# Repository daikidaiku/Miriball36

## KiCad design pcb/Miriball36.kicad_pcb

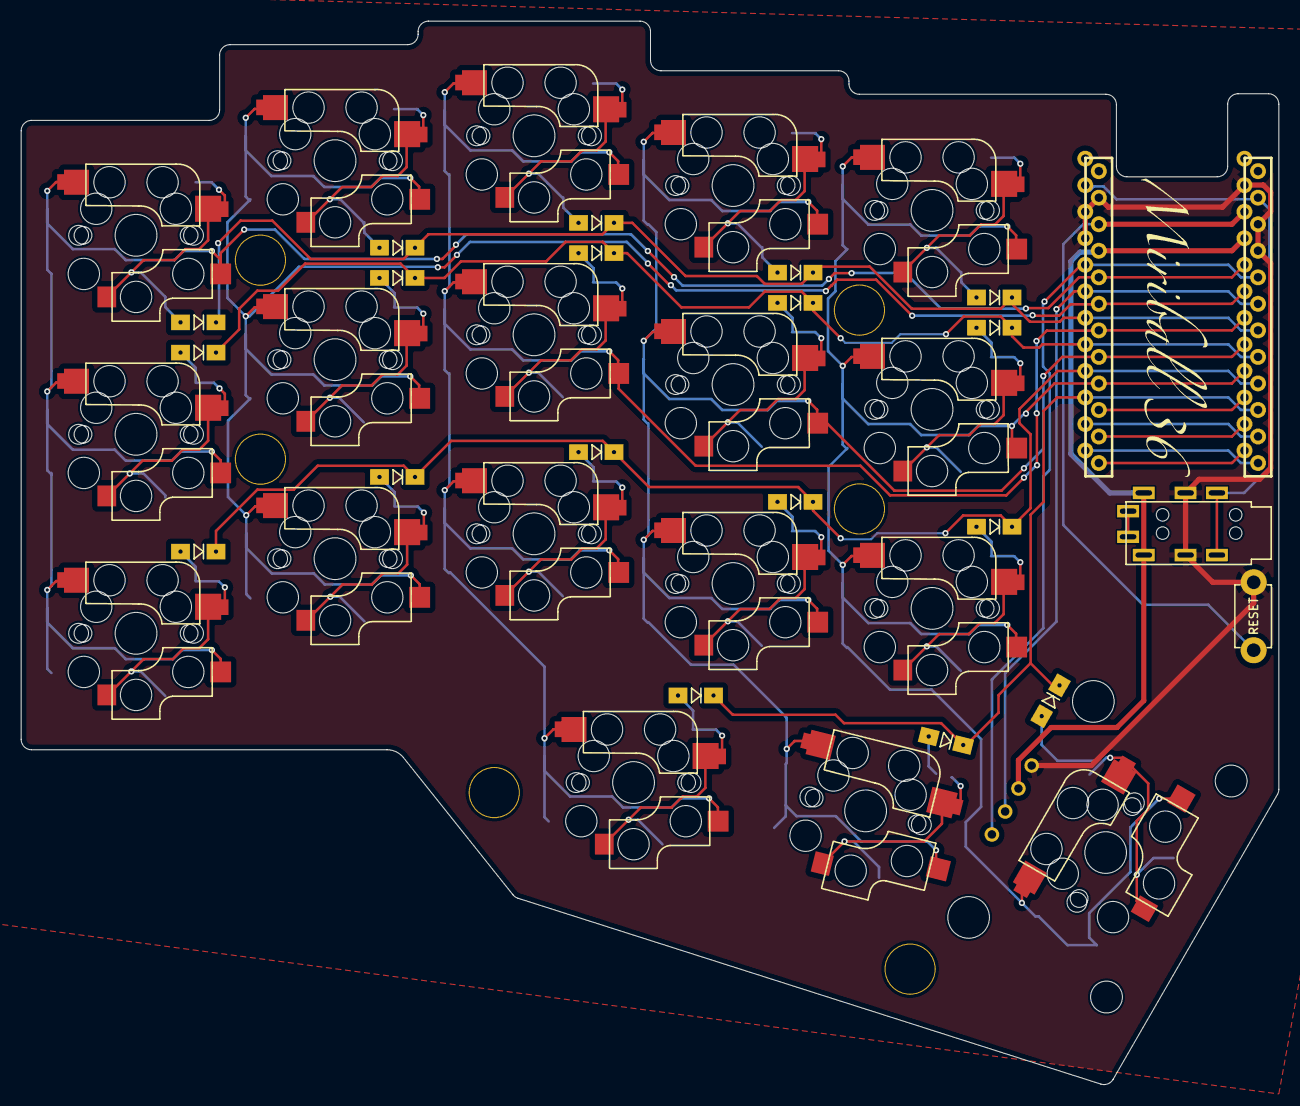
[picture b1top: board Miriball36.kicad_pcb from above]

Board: 2 copper layers, 120.4 x 101.8 mm, 43 parts (0 on the bottom side), 33 nets.

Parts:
D1, D2, D3, D4, D5, D6, D7, D8, D9, D10, D11, D12, D13, D14, D15, D16, D17, D18: 1N4148W; Diode_1N4148W
J2: MJ-4PP-9; TRRS_MJ-4PP-9
OL1: OLED; OLED_4Pin
SW1, SW2, SW3, SW4, SW5, SW6, SW7, SW8, SW9, SW10, SW11, SW12, SW13, SW14, SW15, SW16, SW17: SW_PUSH; CherryMX_KailhLowProfile_Hotswap_edge
SW18: SW_PUSH; CherryMX_KailhLowProfile_Hotswap_edge_stab
SW19: SW_RESET; RESET
TH3, TH3#2, TH3#3: HOLE; HOLE_M2_TH
U1: ProMicro; ProMicro2

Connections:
GND: J2.C, OL1.4 (GND), SW19.2, U1.3 (GND), U1.4 (GND), U1.23 (GND)
unnamed: D1.2 (A), SW1.2
unnamed: D2.2 (A), SW2.2
unnamed: D3.2 (A), SW3.2
unnamed: D4.2 (A), SW4.2
unnamed: D5.2 (A), SW5.2
unnamed: D6.2 (A), SW6.2
unnamed: D7.2 (A), SW7.2
unnamed: D8.2 (A), SW8.2
unnamed: D9.2 (A), SW9.2
unnamed: D10.2 (A), SW10.2
unnamed: D11.2 (A), SW11.2
unnamed: D12.2 (A), SW12.2
unnamed: D13.2 (A), SW13.2
unnamed: D14.2 (A), SW14.2
unnamed: D15.2 (A), SW15.2
unnamed: D16.2 (A), SW16.2
unnamed: D17.2 (A), SW17.2
unnamed: D18.2 (A), SW18.2
VCC: J2.D, OL1.3 (VCC), U1.21 (VCC)
col0: SW1.1, SW6.1, SW11.1, U1.20 (F4/A3)
col1: SW2.1, SW7.1, SW12.1, U1.19 (F5/A2)
col2: SW3.1, SW8.1, SW13.1, SW16.1, U1.18 (F6/A1)
col3: SW4.1, SW9.1, SW14.1, SW17.1, U1.17 (F7/A0)
col4: SW5.1, SW10.1, SW15.1, SW18.1, U1.16 (B1/15)
data: J2.B, U1.2 (RX1/D2)
reset: SW19.1, U1.22 (RST)
row0: D1.1 (K), D2.1 (K), D3.1 (K), D4.1 (K), D5.1 (K), U1.7 (4/D4)
row1: D6.1 (K), D7.1 (K), D8.1 (K), D9.1 (K), D10.1 (K), U1.8 (5/C6)
row2: D11.1 (K), D12.1 (K), D13.1 (K), D14.1 (K), D15.1 (K), U1.9 (6/D7)
row3: D16.1 (K), D17.1 (K), D18.1 (K), U1.10 (7/E6)
scl: OL1.2 (SCL), U1.6 (3/D0/SCL)
sda: OL1.1 (SDA), U1.5 (2/D1/SDA)

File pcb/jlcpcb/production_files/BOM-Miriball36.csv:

Comment,Designator,Footprint,LCSC
1N4148W,D11,Diode_1N4148W,
HOLE,TH3,HOLE_M2_TH,
1N4148W,D8,Diode_1N4148W,
SW_PUSH,SW1,CherryMX_KailhLowProfile_Hotswap_edge,
SW_PUSH,SW4,CherryMX_KailhLowProfile_Hotswap_edge,
SW_PUSH,SW7,CherryMX_KailhLowProfile_Hotswap_edge,
SW_PUSH,SW18,CherryMX_KailhLowProfile_Hotswap_edge_stab,
OLED,OL1,OLED_4Pin,
SW_PUSH,SW16,CherryMX_KailhLowProfile_Hotswap_edge,
MJ-4PP-9,J2,TRRS_MJ-4PP-9,
SW_PUSH,SW2,CherryMX_KailhLowProfile_Hotswap_edge,
SW_PUSH,SW6,CherryMX_KailhLowProfile_Hotswap_edge,
SW_PUSH,SW3,CherryMX_KailhLowProfile_Hotswap_edge,
1N4148W,D9,Diode_1N4148W,
1N4148W,D10,Diode_1N4148W,
1N4148W,D14,Diode_1N4148W,
1N4148W,D18,Diode_1N4148W,
1N4148W,D17,Diode_1N4148W,
1N4148W,D5,Diode_1N4148W,
1N4148W,D7,Diode_1N4148W,
1N4148W,D6,Diode_1N4148W,
1N4148W,D13,Diode_1N4148W,
SW_PUSH,SW8,CherryMX_KailhLowProfile_Hotswap_edge,
SW_PUSH,SW15,CherryMX_KailhLowProfile_Hotswap_edge,
SW_PUSH,SW5,CherryMX_KailhLowProfile_Hotswap_edge,
SW_RESET,SW19,RESET,
SW_PUSH,SW13,CherryMX_KailhLowProfile_Hotswap_edge,
1N4148W,D2,Diode_1N4148W,
1N4148W,D4,Diode_1N4148W,
SW_PUSH,SW17,CherryMX_KailhLowProfile_Hotswap_edge,
1N4148W,D1,Diode_1N4148W,
1N4148W,D12,Diode_1N4148W,
1N4148W,D16,Diode_1N4148W,
SW_PUSH,SW10,CherryMX_KailhLowProfile_Hotswap_edge,
1N4148W,D3,Diode_1N4148W,
SW_PUSH,SW14,CherryMX_KailhLowProfile_Hotswap_edge,
ProMicro,U1,ProMicro2,
SW_PUSH,SW11,CherryMX_KailhLowProfile_Hotswap_edge,
SW_PUSH,SW12,CherryMX_KailhLowProfile_Hotswap_edge,
1N4148W,D15,Diode_1N4148W,
SW_PUSH,SW9,CherryMX_KailhLowProfile_Hotswap_edge,

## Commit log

2024-05-28 add files
2024-05-28 add plate
2024-05-30 add logo & pin for trackball
2024-05-31 add hole
2024-06-10 PCBを更新
2024-06-10 add top plate
2024-06-10 remove plate
2024-06-10 change hole
2024-06-10 add bottom plate
2024-06-10 add Gerber
2024-06-10 add top Gerber
2024-07-10 Create LICENSE
